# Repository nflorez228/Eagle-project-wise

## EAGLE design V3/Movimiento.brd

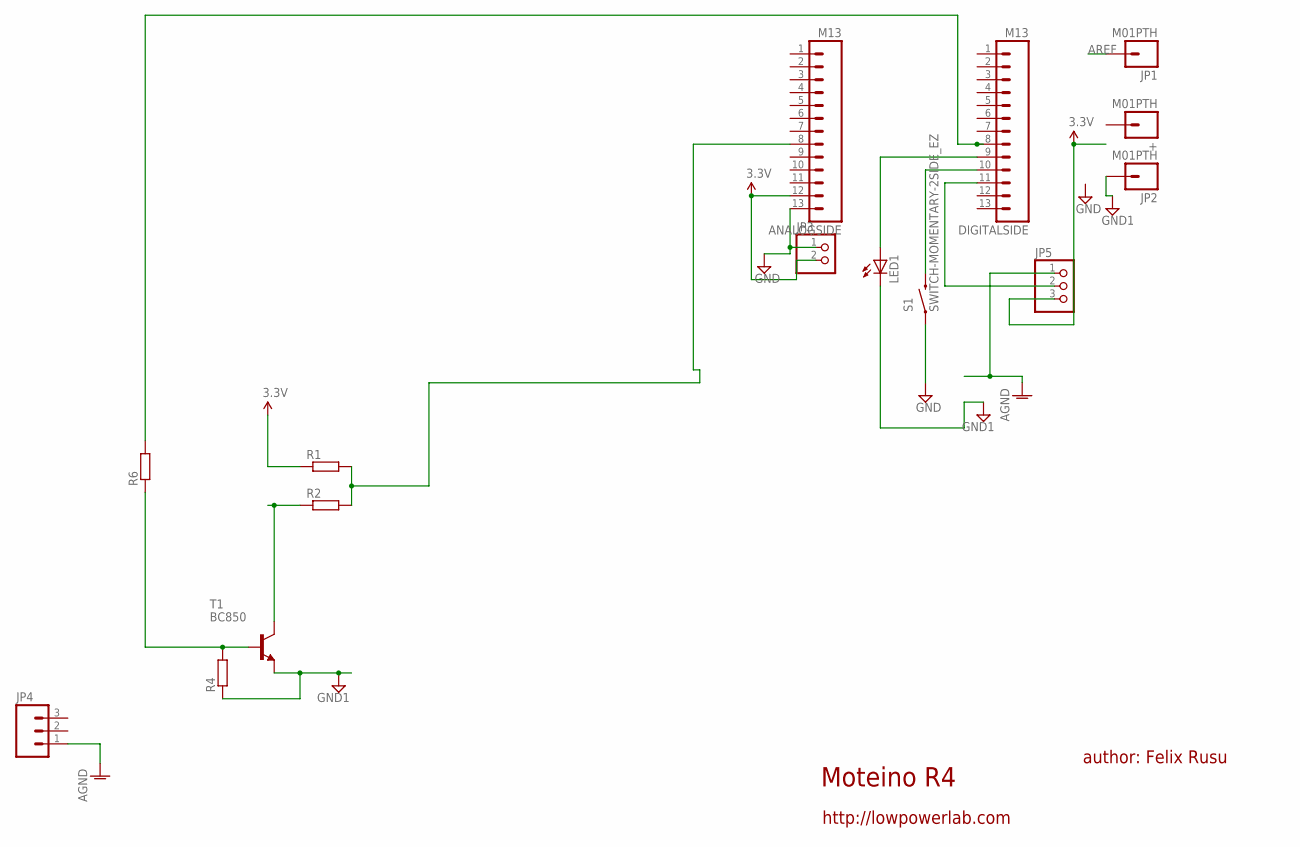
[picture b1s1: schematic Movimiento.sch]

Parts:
+: M01PTH; 1X01
ANALOGSIDE: M13; 1X13
DIGITALSIDE: M13; 1X13
JP1, JP2: M01PTH; 1X01
JP3: PINHD-1X2; 1X02
JP4: M03PTH; 1X03
JP5: PINHD-1X3; 1X03
LED1: LED3MM
R1, R2: R-EU_0204/7; 0204/7
R4, R6: R-EU_M1206; M1206
S1: SWITCH-MOMENTARY-2SIDE_EZ; TACTILE-PTH-SIDEEZ
T1: BC850; SOT23

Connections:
AGND: JP4.1, JP5.1
AREF: JP1.1
GND: ANALOGSIDE.13, JP3.1, S1.1
GND1: JP2.1, LED1.K (C), R4.1, T1.2 (E)
unnamed: DIGITALSIDE.10, S1.2
unnamed: DIGITALSIDE.11, JP5.2
unnamed: DIGITALSIDE.8, R6.2
unnamed: DIGITALSIDE.9, LED1.A
unnamed: ANALOGSIDE.8, R1.2, R2.2
unnamed: R2.1, T1.3 (C)
unnamed: R4.2, R6.1, T1.1 (B)
VCC: ANALOGSIDE.12, JP3.2, JP5.3, R1.1

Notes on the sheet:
Moteino R4
author: Felix Rusu
http://lowpowerlab.com

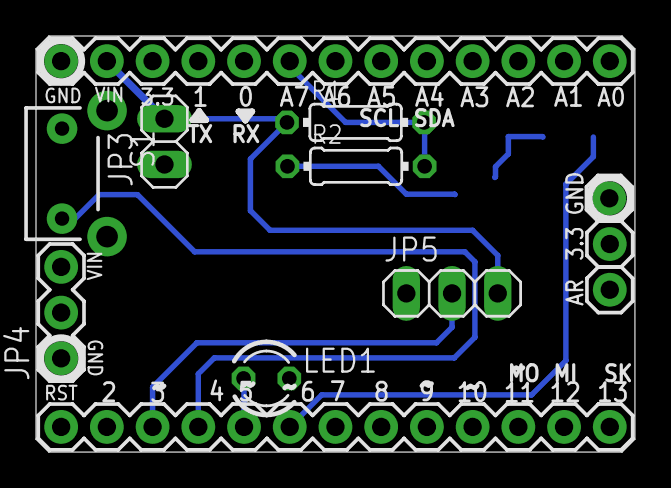
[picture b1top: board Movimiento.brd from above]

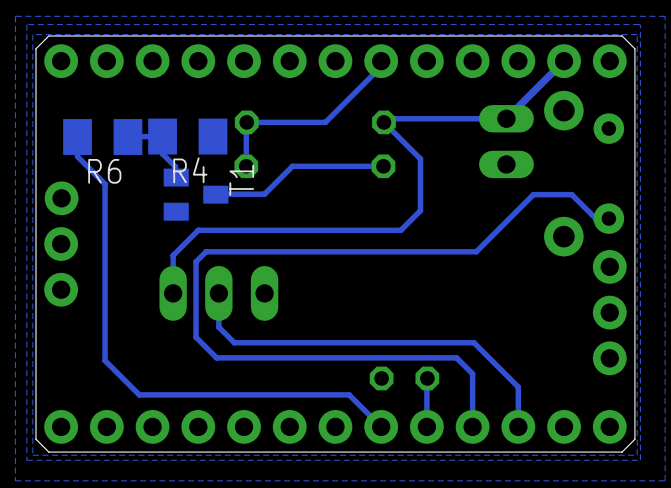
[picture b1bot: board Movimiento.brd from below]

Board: 2 copper layers, 33.3 x 23.1 mm, 15 parts (3 on the bottom side), 11 nets.

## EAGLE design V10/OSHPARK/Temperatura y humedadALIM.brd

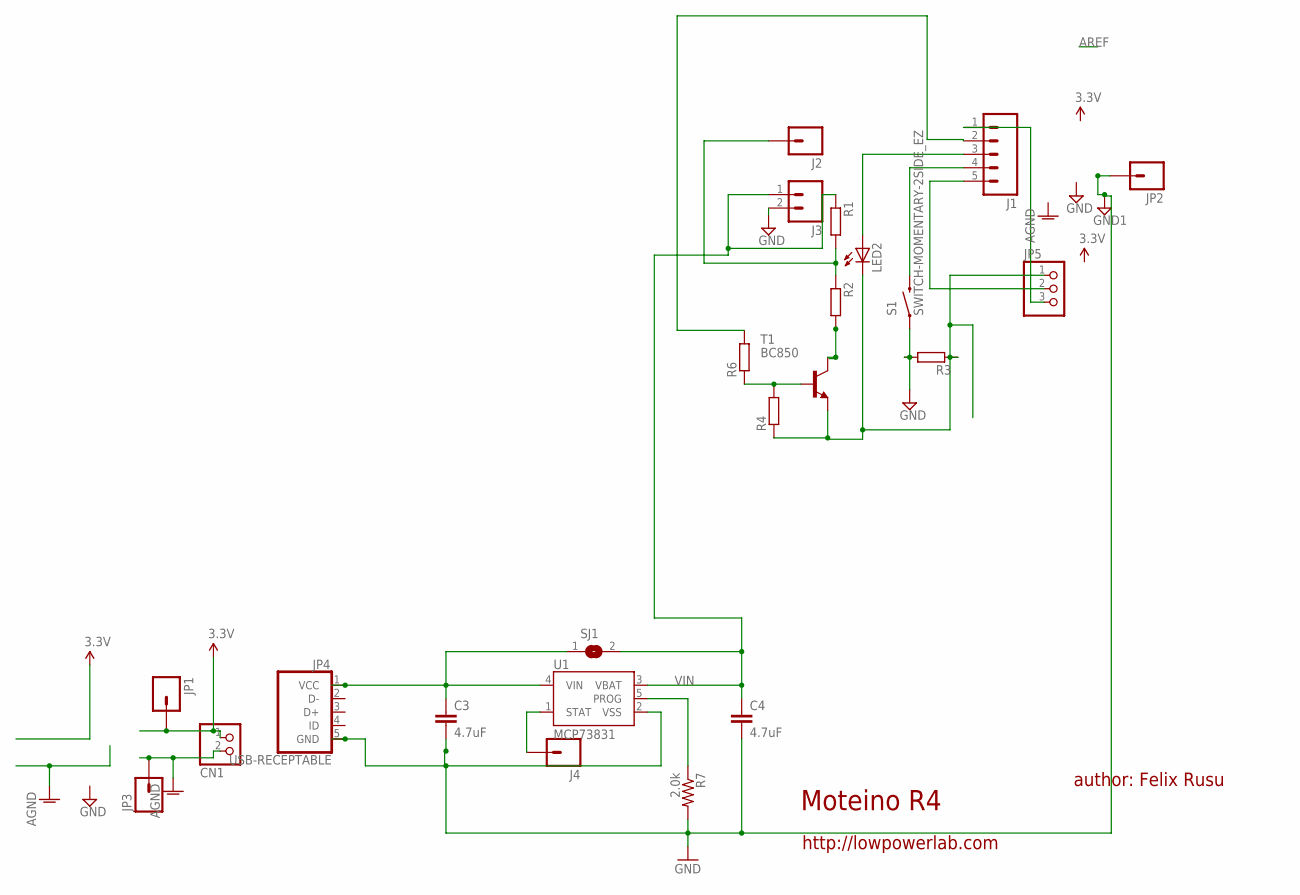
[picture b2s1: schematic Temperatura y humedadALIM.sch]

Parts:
C3, C4: 4.7uF; 0603-CAP
CN1: JST_2PIN-SMT; JST-PH-2-SMT
J1: M05PTH; 1X05
J2, J4: M01PTH; 1X01
J3: M02PTH; 1X02
JP1, JP2, JP3: M01PTH; 1X01
JP4: USB-RECEPTABLE; FCI-10103594-0001LF
JP5: PINHD-1X3; 1X03
LED2: LED3MM
R1, R2: R-EU_0204/7; 0204/7
R3, R4, R6: R-EU_M1206; M1206
R7: 2.0k; 0603-RES
S1: SWITCH-MOMENTARY-2SIDE_EZ; TACTILE-PTH-SIDEEZ
SJ1: SJ
T1: BC850; SOT23
U1: MCP73831; SOT23-5

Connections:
AGND: CN1.2 (1), JP3.1
GND: J3.2, R3.2, S1.1
GND1: C3.2, C4.2, JP2.1, JP4.5 (GND), R7.2, U1.2 (VSS)
unnamed: J1.4, S1.2
unnamed: J1.5, JP5.2
unnamed: J1.1, JP5.3
unnamed: JP5.1, LED2.K (C), R3.1, R4.1, T1.2 (E)
unnamed: C3.1, JP4.1 (VCC), SJ1.1, U1.4 (VIN)
unnamed: J2.1, R1.2, R2.1
unnamed: R2.2, T1.3 (C)
unnamed: R4.2, R6.1, T1.1 (B)
unnamed: J1.2, R6.2
unnamed: J1.3, LED2.A
unnamed: J4.1, U1.1 (STAT)
PROG: R7.1, U1.5 (PROG)
VCC: CN1.1 (2), JP1.1
VIN: C4.1, J3.1, R1.1, SJ1.2, U1.3 (VBAT)

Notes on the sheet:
Moteino R4
author: Felix Rusu
http://lowpowerlab.com

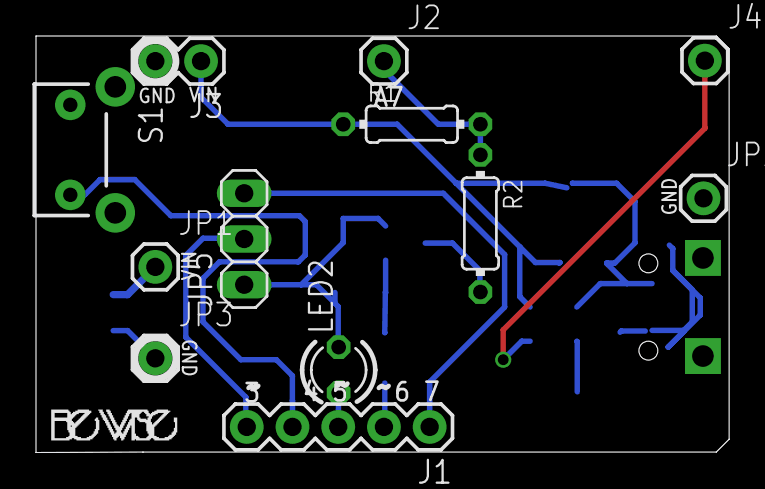
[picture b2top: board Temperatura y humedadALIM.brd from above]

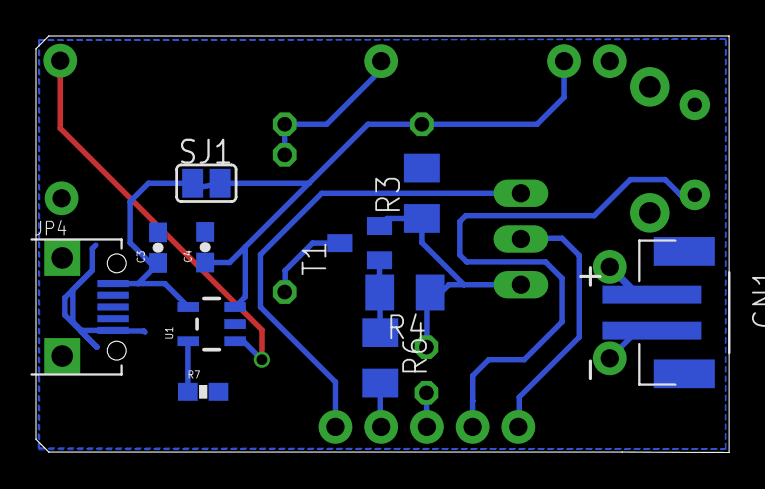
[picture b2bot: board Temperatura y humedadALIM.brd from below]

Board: 2 copper layers, 38.5 x 23.1 mm, 23 parts (11 on the bottom side), 17 nets.

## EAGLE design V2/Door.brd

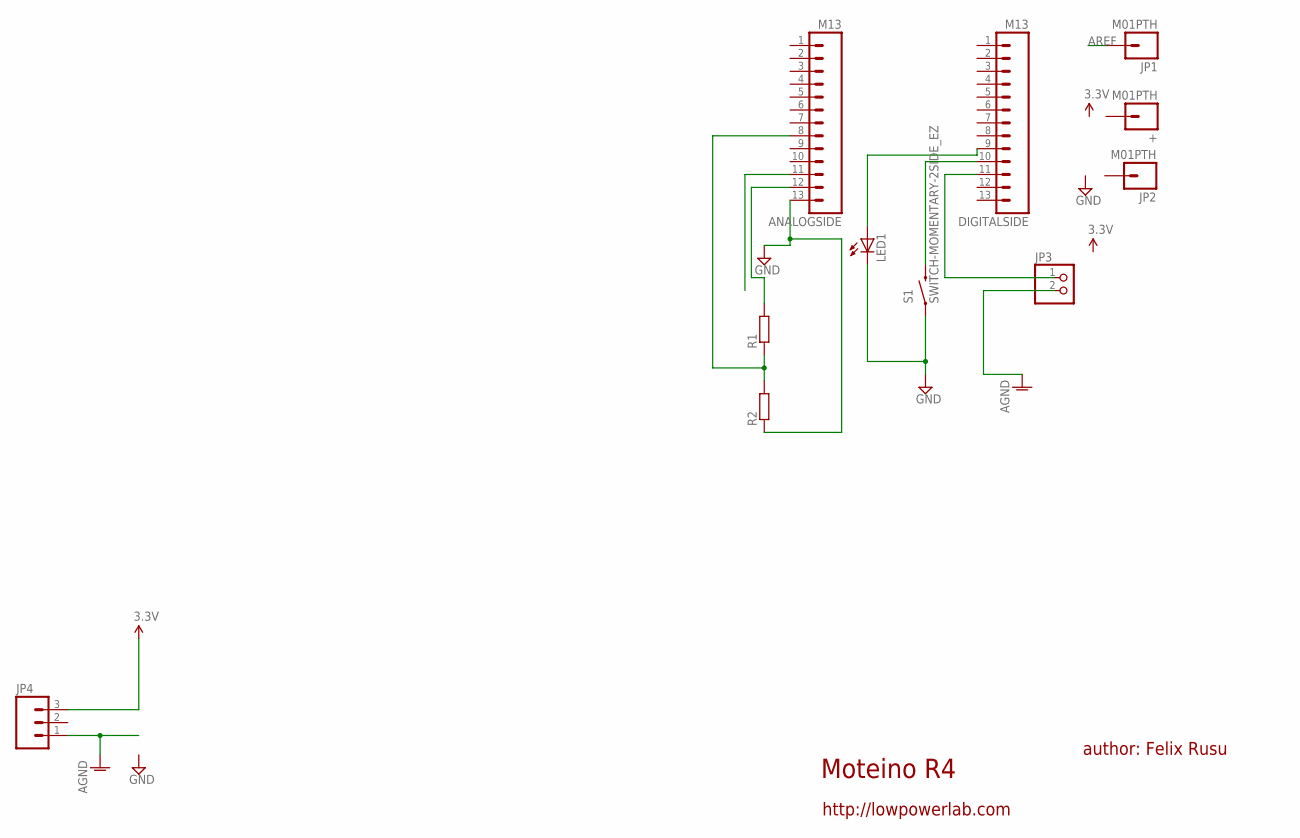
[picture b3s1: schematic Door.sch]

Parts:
+: M01PTH; 1X01
ANALOGSIDE: M13; 1X13
DIGITALSIDE: M13; 1X13
JP1, JP2: M01PTH; 1X01
JP3: PINHD-1X2; 1X02
JP4: M03PTH; 1X03
LED1: LED3MM
R1, R2: R-EU_0204/7; 0204/7
S1: SWITCH-MOMENTARY-2SIDE_EZ; TACTILE-PTH-SIDEEZ

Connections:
AGND: JP3.2, JP4.1
AREF: JP1.1
GND: ANALOGSIDE.13, LED1.K (C), R2.1, S1.1
unnamed: DIGITALSIDE.10, S1.2
unnamed: DIGITALSIDE.11, JP3.1
unnamed: DIGITALSIDE.9, LED1.A
unnamed: ANALOGSIDE.12, R1.2
unnamed: ANALOGSIDE.8, R1.1, R2.2
VCC: JP4.3

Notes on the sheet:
Moteino R4
author: Felix Rusu
http://lowpowerlab.com

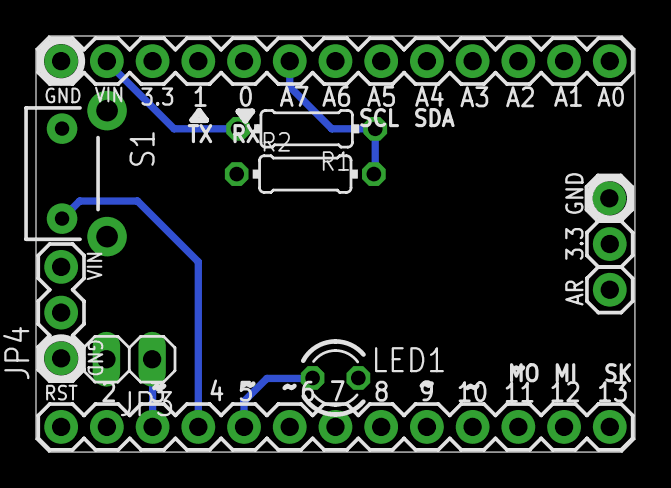
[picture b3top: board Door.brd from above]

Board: 2 copper layers, 33.3 x 23.1 mm, 11 parts (0 on the bottom side), 7 nets.

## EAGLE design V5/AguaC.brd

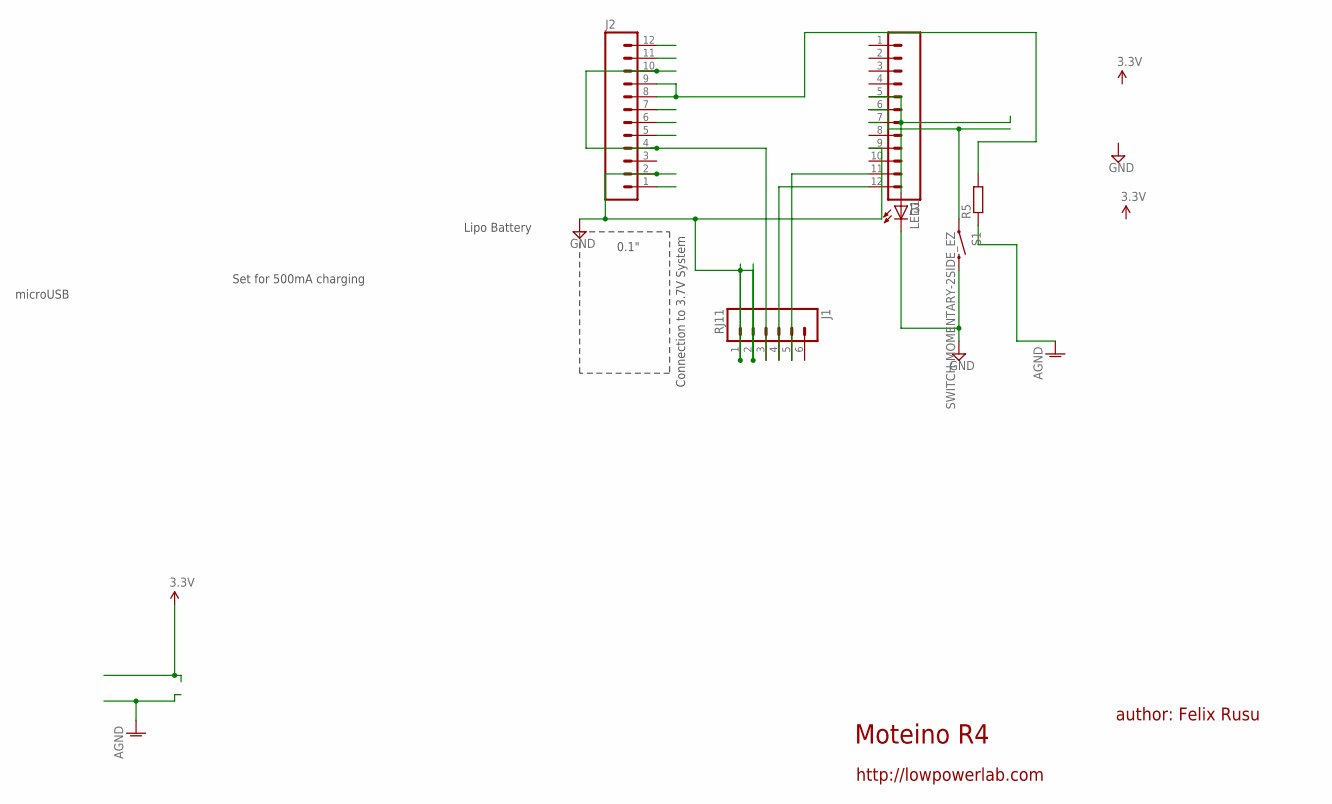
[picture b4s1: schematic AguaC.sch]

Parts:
J1: RJ11; RJ11-6
J2, J3: M12PTH; 1X12
LED1: LED3MM
R5: R-EU_0204/7; 0204/7
S1: SWITCH-MOMENTARY-2SIDE_EZ; TACTILE-PTH-SIDEEZ

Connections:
AGND: R5.1
GND: J1.1, J1.2, J2.2, J3.9, LED1.K (C), S1.2
unnamed: J3.6, S1.1
unnamed: J3.5, LED1.A
unnamed: J1.4, J3.12
unnamed: J1.5, J3.11
unnamed: J2.8, J2.9, R5.2
VIN: J1.3, J2.4, J2.10

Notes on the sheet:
Moteino R4
author: Felix Rusu
http://lowpowerlab.com
Set for 500mA charging
Connection to 3.7V System
0.1"
microUSB
Lipo Battery

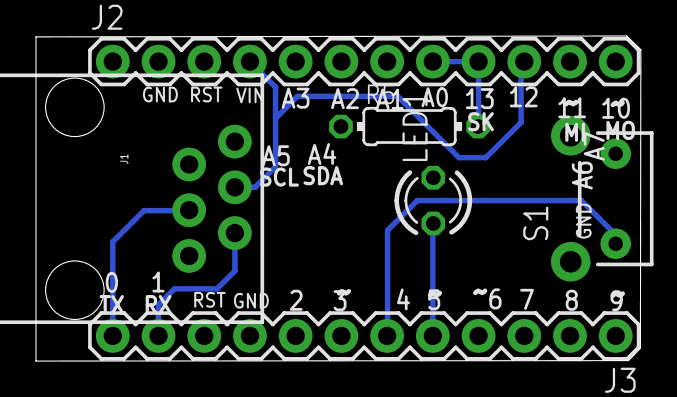
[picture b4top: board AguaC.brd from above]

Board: 2 copper layers, 33.6 x 18.1 mm, 6 parts (0 on the bottom side), 7 nets.

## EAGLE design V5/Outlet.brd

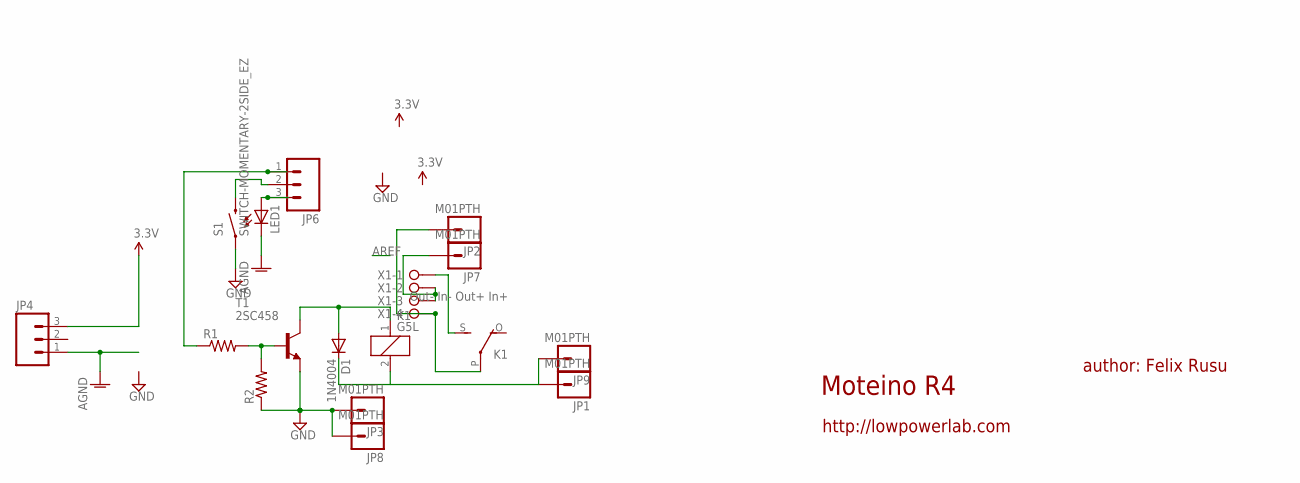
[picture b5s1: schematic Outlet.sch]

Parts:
D1: 1N4004; DO41-10
JP1, JP2, JP3, JP7, JP8, JP9: M01PTH; 1X01
JP4, JP6: M03PTH; 1X03
K1: G5L; G5LE
LED1: LED3MM
R1, R2: R-US_0204/7; 0204/7
S1: SWITCH-MOMENTARY-2SIDE_EZ; TACTILE-PTH-SIDEEZ
T1: 2SC458; TO92-ECB
X1: Out- In- Out+ In+; W237-4P; MPN Out-

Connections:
AGND: JP4.1, LED1.K (C)
GND: JP3.1, JP8.1, R2.1, S1.1, T1.E
unnamed: JP6.2, S1.2
unnamed: JP7.1, X1.2, X1.3
unnamed: JP6.3, LED1.A
unnamed: R1.2, R2.2, T1.B
unnamed: D1.A, K1.1, T1.C
unnamed: D1.C, JP1.1, JP9.1, K1.2
unnamed: K1.S, X1.1
unnamed: JP2.1, K1.P, X1.4
unnamed: JP6.1, R1.1
VCC: JP4.3

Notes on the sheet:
Moteino R4
author: Felix Rusu
http://lowpowerlab.com

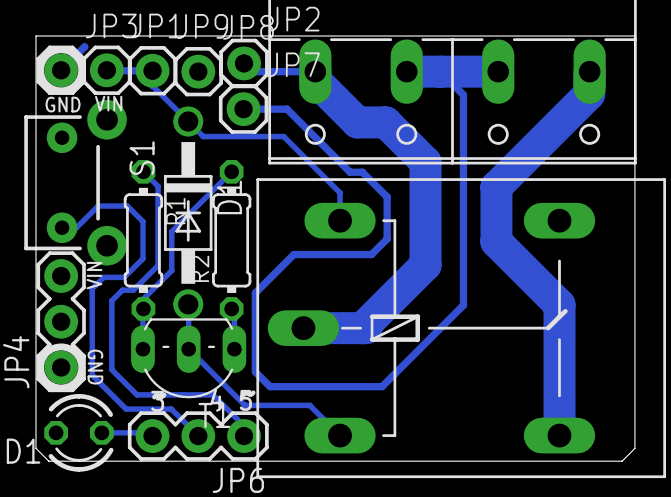
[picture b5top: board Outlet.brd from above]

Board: 2 copper layers, 33.3 x 23.6 mm, 16 parts (0 on the bottom side), 11 nets.

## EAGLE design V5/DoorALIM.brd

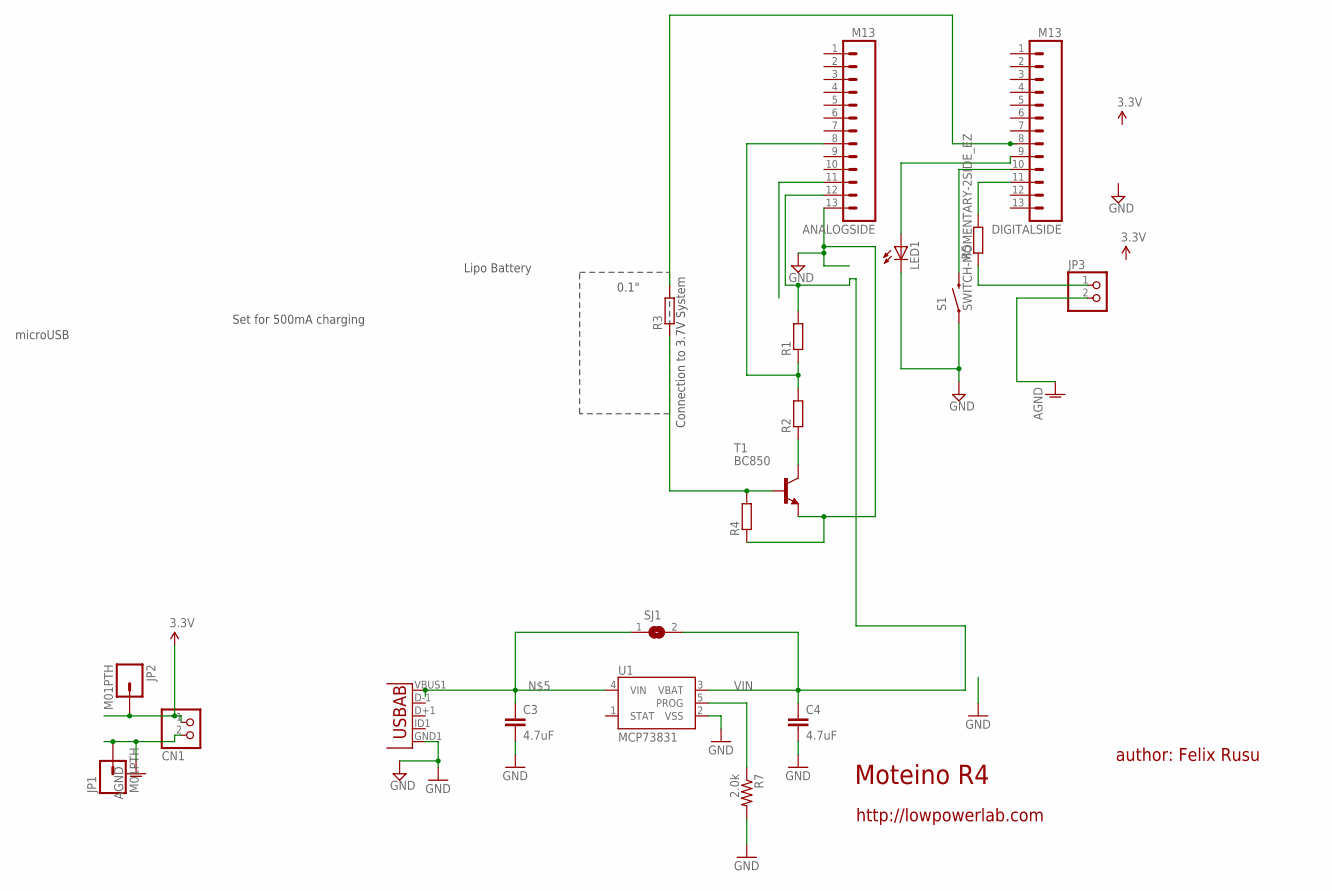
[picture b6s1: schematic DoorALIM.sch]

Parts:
ANALOGSIDE: M13; 1X13
C3, C4: 4.7uF; 0603-CAP
CN1: JST_2PIN-SMT; JST-PH-2-SMT
DIGITALSIDE: M13; 1X13
JP1, JP2: M01PTH; 1X01
JP3: PINHD-1X2; 1X02
JP9: Micro USB; USB-AB-MICRO-SMD_V03
LED1: LED3MM
R1, R2, R5: R-EU_0204/7; 0204/7
R3, R4: R-EU_M1206; M1206
R7: 2.0k; 0603-RES
S1: SWITCH-MOMENTARY-2SIDE_EZ; TACTILE-PTH-SIDEEZ
SJ1: SJ
T1: BC850; SOT23
U1: MCP73831; SOT23-5

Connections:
AGND: CN1.2 (1), JP1.1, JP3.2
GND: ANALOGSIDE.13, C3.2, C4.2, JP9.GND1 (GND), LED1.K (C), R4.1, R7.2, S1.1, T1.2 (E), U1.2 (VSS)
unnamed: DIGITALSIDE.10, S1.2
unnamed: JP3.1, R5.1
unnamed: DIGITALSIDE.9, LED1.A
unnamed: C3.1, JP9.VBUS1 (VBUS), SJ1.1, U1.4 (VIN)
unnamed: ANALOGSIDE.8, R1.1, R2.2
unnamed: R2.1, T1.3 (C)
unnamed: R3.1, R4.2, T1.1 (B)
unnamed: DIGITALSIDE.8, R3.2
unnamed: DIGITALSIDE.11, R5.2
PROG: R7.1, U1.5 (PROG)
VCC: CN1.1 (2), JP2.1
VIN: ANALOGSIDE.12, C4.1, R1.2, SJ1.2, U1.3 (VBAT)

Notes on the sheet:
Moteino R4
author: Felix Rusu
http://lowpowerlab.com
Set for 500mA charging
Connection to 3.7V System
0.1"
microUSB
Lipo Battery

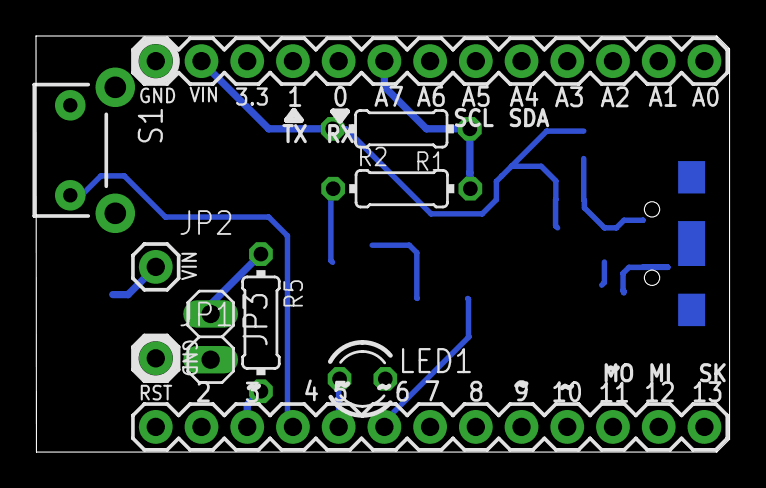
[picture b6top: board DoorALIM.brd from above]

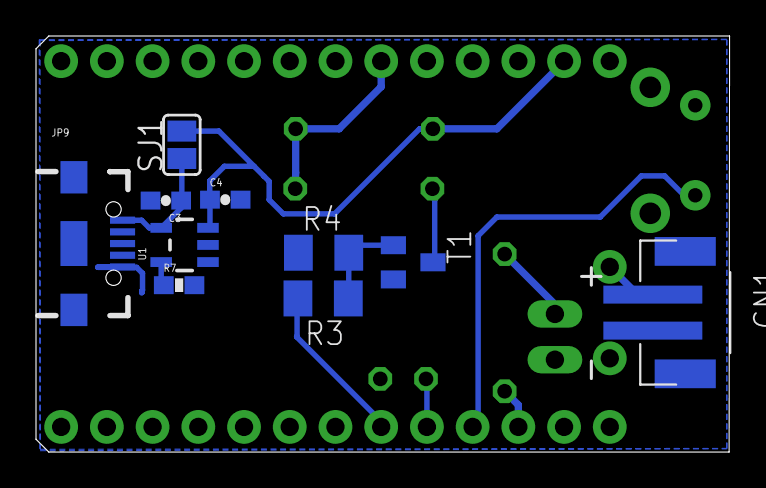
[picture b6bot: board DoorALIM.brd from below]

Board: 2 copper layers, 38.5 x 23.1 mm, 20 parts (10 on the bottom side), 14 nets.

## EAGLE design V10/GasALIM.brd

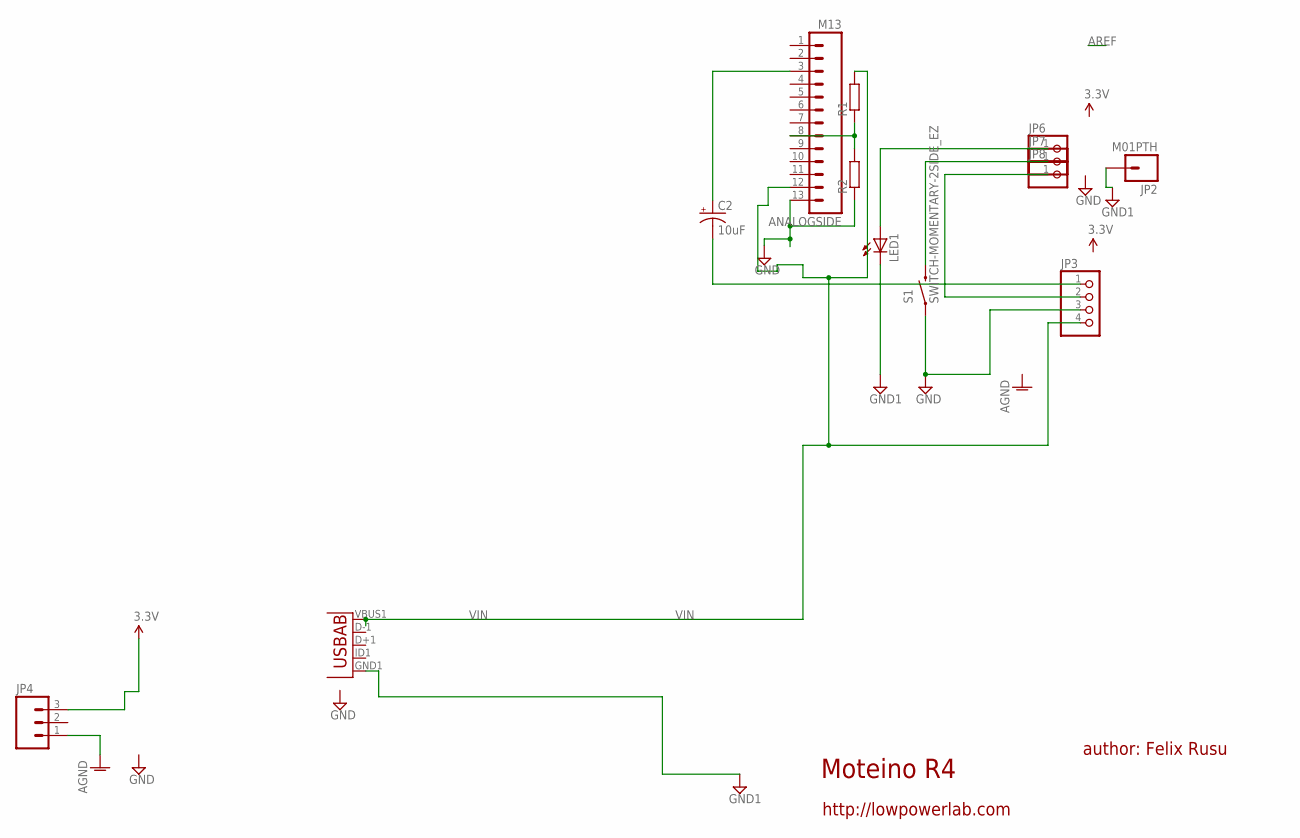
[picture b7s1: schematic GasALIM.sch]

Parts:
ANALOGSIDE: M13; 1X13
C2: 10uF; EIA3216
JP2: M01PTH; 1X01
JP3: PINHD-1X4; 1X04
JP4: M03PTH; 1X03
JP6, JP7, JP8: PINHD-1X1; 1X01
JP9: Micro USB; USB-AB-MICRO-SMD_V03
LED1: LED3MM
R1, R2: R-EU_0204/7; 0204/7
S1: SWITCH-MOMENTARY-2SIDE_EZ; TACTILE-PTH-SIDEEZ

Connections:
AGND: JP4.1
GND: ANALOGSIDE.13, JP3.3, R2.1, S1.1
GND1: JP2.1, JP9.GND1 (GND), LED1.K (C)
unnamed: JP7.1, S1.2
unnamed: JP3.2, JP8.1
unnamed: C2.C (-), JP3.1
unnamed: ANALOGSIDE.3, C2.A (+)
unnamed: ANALOGSIDE.8, R1.1, R2.2
unnamed: JP6.1, LED1.A
VCC: JP4.3
VIN: ANALOGSIDE.12, JP3.4, JP9.VBUS1 (VBUS), R1.2

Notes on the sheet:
Moteino R4
author: Felix Rusu
http://lowpowerlab.com

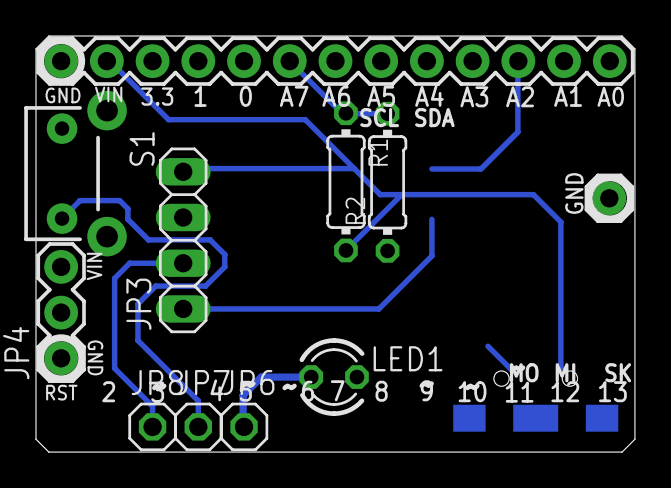
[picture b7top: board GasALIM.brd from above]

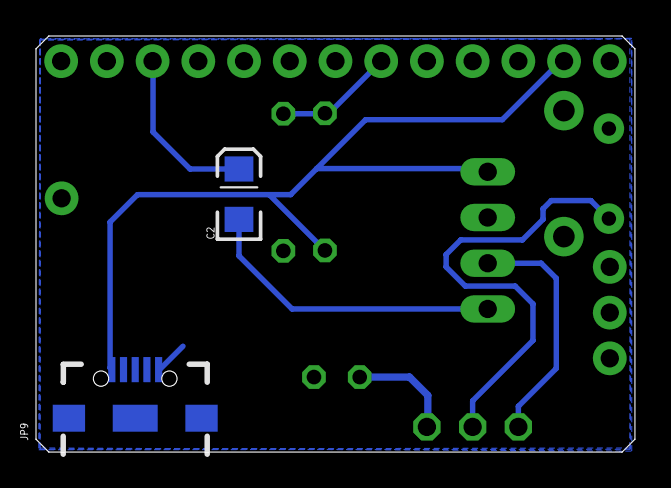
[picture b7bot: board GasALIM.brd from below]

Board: 2 copper layers, 33.3 x 23.1 mm, 13 parts (2 on the bottom side), 9 nets.

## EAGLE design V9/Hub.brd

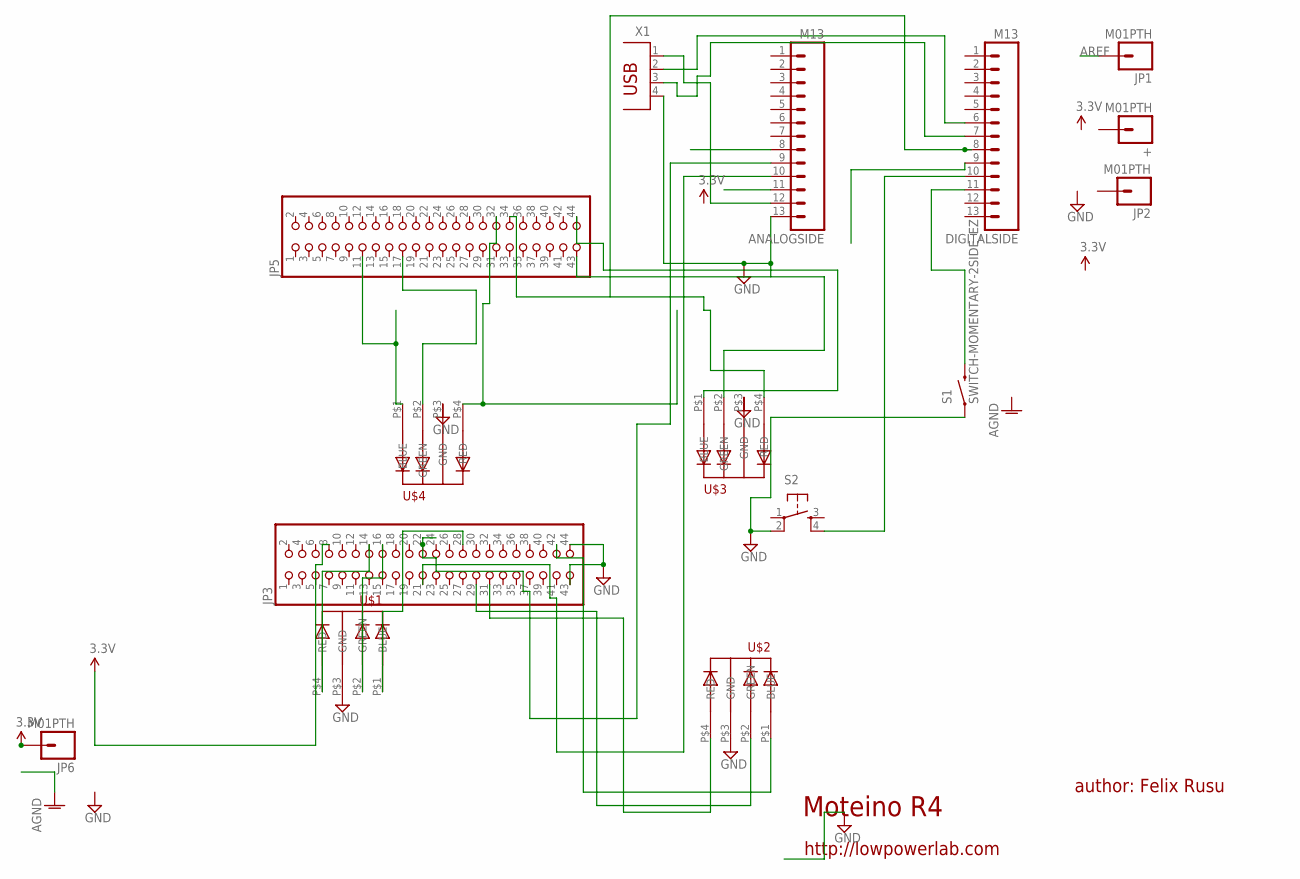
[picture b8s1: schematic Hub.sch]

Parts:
+: M01PTH; 1X01
ANALOGSIDE: M13; 1X13
DIGITALSIDE: M13; 1X13
JP1, JP2, JP6: M01PTH; 1X01
JP3, JP5: PINHD-2X22; 2X22
S1: SWITCH-MOMENTARY-2SIDE_EZ; TACTILE-PTH-SIDEEZ
S2: TAC_SWITCHPTH; TACTILE-PTH
U$1, U$2, U$3, U$4: 5MMRGBLED; LED5MMRGB
X1: PN87520

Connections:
AREF: JP1.1
GND: ANALOGSIDE.13, JP3.43, JP3.44, S1.1, S2.2, U$1.P$3 (GND), U$2.P$3 (GND), U$3.P$3 (GND), U$4.P$3 (GND), X1.4
unnamed: DIGITALSIDE.10, S2.4
unnamed: JP3.14, U$1.P$4 (RED)
unnamed: JP3.28, U$1.P$1 (BLUE)
unnamed: JP3.16, U$1.P$2 (GREEN)
unnamed: DIGITALSIDE.11, S1.2
unnamed: JP3.42, U$2.P$1 (BLUE)
unnamed: ANALOGSIDE.9, JP3.22
unnamed: JP3.29, U$2.P$2 (GREEN)
unnamed: JP3.31, U$2.P$4 (RED)
unnamed: JP5.11, U$4.P$1 (BLUE)
unnamed: JP5.17, U$4.P$2 (GREEN)
unnamed: JP5.32, U$4.P$4 (RED)
unnamed: JP5.43, U$3.P$2 (GREEN)
unnamed: JP5.44, U$3.P$1 (BLUE)
unnamed: JP5.34, U$3.P$4 (RED)
unnamed: ANALOGSIDE.10, JP3.21
unnamed: DIGITALSIDE.7, X1.3
unnamed: ANALOGSIDE.12, X1.1
unnamed: DIGITALSIDE.6, X1.2
VCC: JP3.8, JP6.1

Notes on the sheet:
Moteino R4
author: Felix Rusu
http://lowpowerlab.com

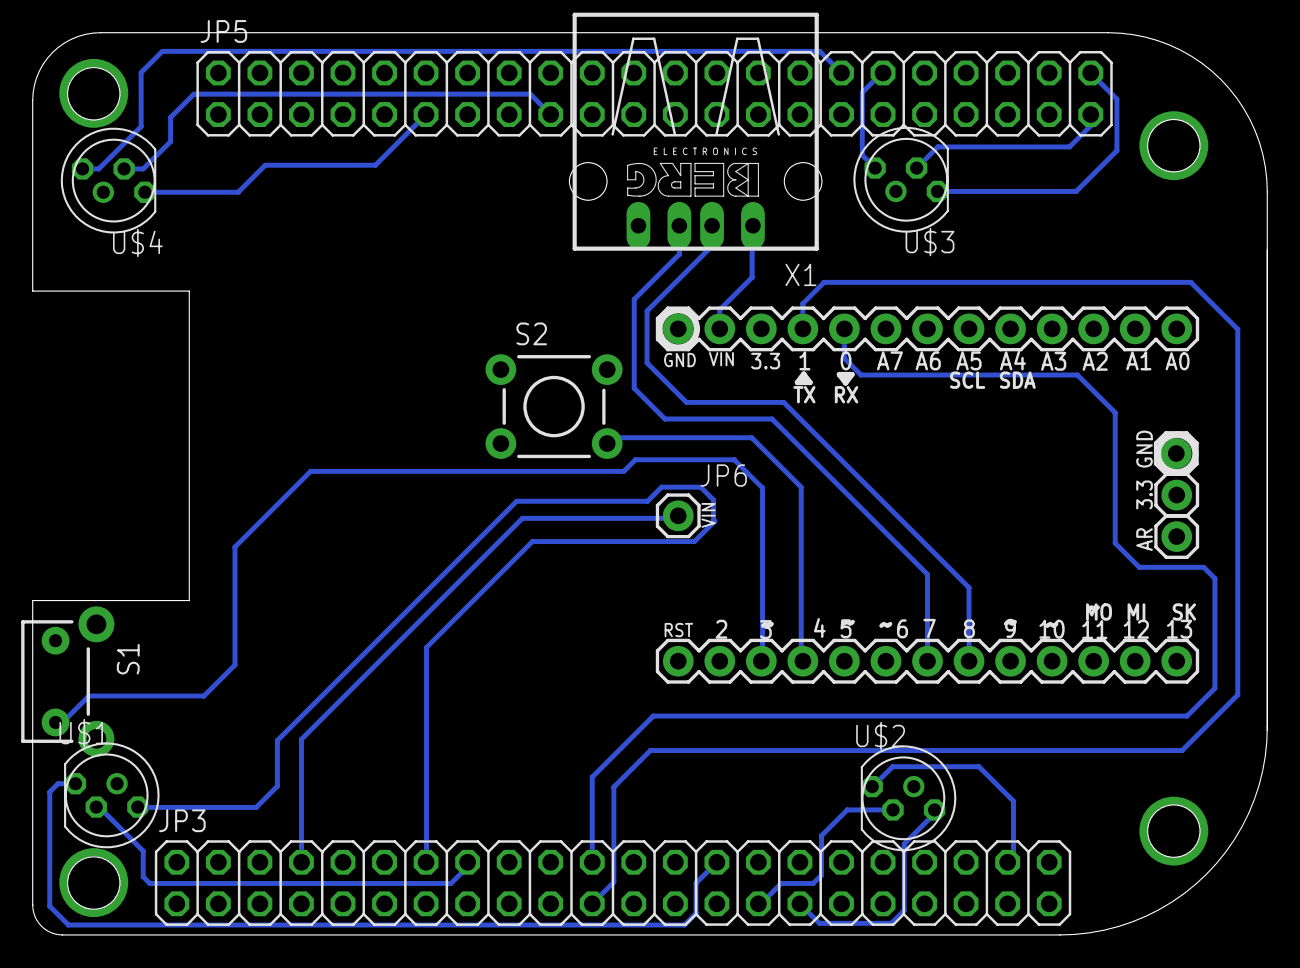
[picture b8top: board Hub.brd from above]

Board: 2 copper layers, 75.5 x 55.2 mm, 15 parts (0 on the bottom side), 21 nets.

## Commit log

2020-03-30 Migration from gitlab to github

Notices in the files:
parts and their libraries:
SparkFun-Connectors: Licensing: CC v3.0 Share-Alike You are welcome to use this library for commercial purposes.
SparkFun-Electromechanical: Licensing: Creative Commons ShareAlike 4.0 International - https://creativecommons.org/licenses/by-sa/4.0
